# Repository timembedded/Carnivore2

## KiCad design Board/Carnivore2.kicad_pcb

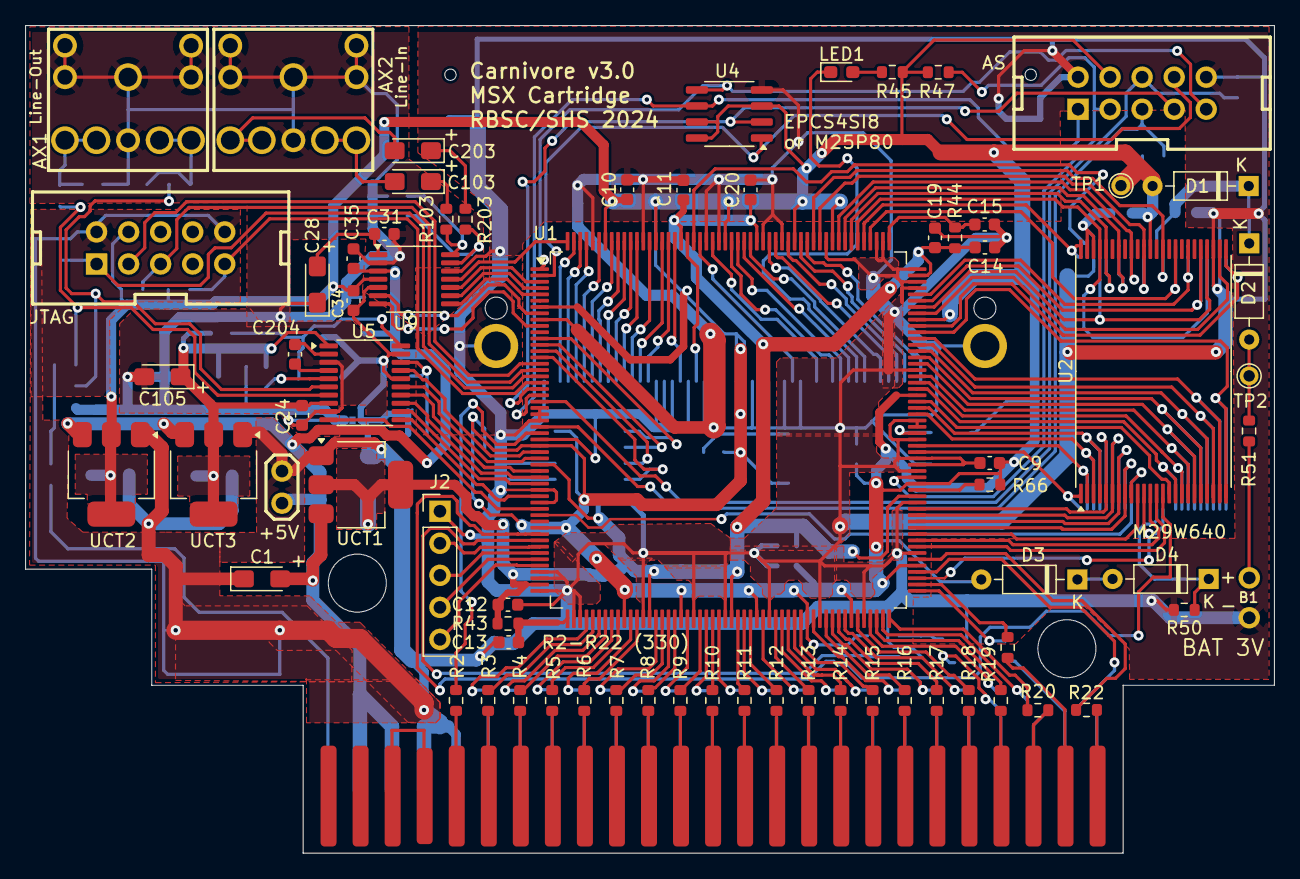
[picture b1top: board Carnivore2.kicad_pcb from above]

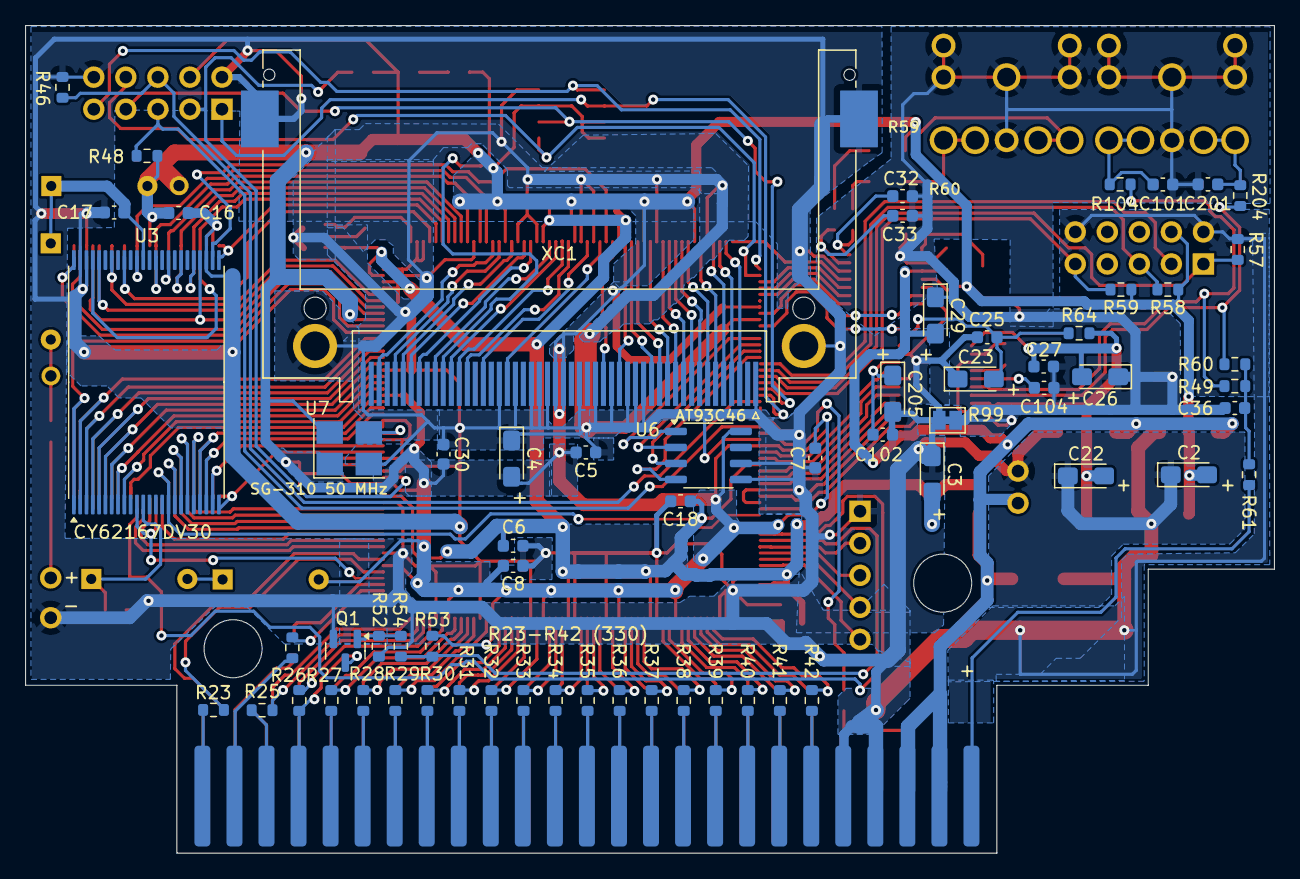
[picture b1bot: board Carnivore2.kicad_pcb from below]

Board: 2 copper layers, 99.0 x 65.6 mm, 139 parts (65 on the bottom side), 215 nets.

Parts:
AX1, AX2: SJ1-3523N; ST-222_1
B1: BAT 3V; BAT
C1, C2, C3, C4, C22, C23, C26, C28, C29, C105, C205: 10uF 10V; CP_EIA-3216-10_Kemet-I_Pad1.58x1.35mm_HandSolder
C5, C6, C7, C8, C9, C10, C11, C12, C13, C14, C15, C16, C17, C18, C19, C20, C24, C25, C27, C30, C31, C32, C33, C34, C35, C102: 100nF; C_0603_1608Metric
C36, C101, C201: 2.2nF; C_0603_1608Metric
C103, C203: 1uF 10V; CP_EIA-3216-10_Kemet-I_Pad1.58x1.35mm_HandSolder
C104, C204: 2.2uF; C_0603_1608Metric
D1, D2, D3, D4: 1N4148; D_DO-35_SOD27_P7.62mm_Horizontal
H1, H2: MountingHole
J1: Conn_01x02_Pin; JUMPER_1
J2: Conn_01x05_Pin; PinHeader_1x05_P2.54mm_Vertical
LED1: 150060YS75000; LED_0603_1608Metric_Pad1.05x0.95mm_HandSolder
Q1: MMBT3904-TP; SOT-23
R2, R3, R4, R5, R6, R7, R8, R9, R10, R11, R12, R13, R14, R15, R16, R17, R18, R19, R20, R21, R22, R23, R24, R25, R26, R27, R28, R29, R30, R31, R32, R33, R34, R35, R36, R37, R38, R39, R40, R41, R42: 330E; R_0603_1608Metric
R43, R44, R64: 10E; R_0603_1608Metric
R45: 220E; R_0603_1608Metric
R46, R47, R48, R50, R52, R66: 10k; R_0603_1608Metric
R49, R54, R60, R61, R104, R204: 470E; R_0603_1608Metric
R51, R57, R58, R59: 1k; R_0603_1608Metric
R53: 4k7; R_0603_1608Metric
R99: 0E; SolderJumper-2_P1.3mm_Bridged_Pad1.0x1.5mm
R103, R203: 75E; R_0603_1608Metric
TP1, TP2: TestPoint; TestPoint_THTPad_D1.5mm_Drill0.9mm
U1: EP2C8Q208C8N; PQFP-208_28x28mm_P0.5mm
U2: MX29LV640ETTI-70G; TSOP-I-48_18.4x12mm_P0.5mm
U3: RMLV1616AGSA-5S#KA0; TSOP-I-48_18.4x12mm_P0.5mm
U4: M25P80-VMN3TPB; SO-8_3.9x4.9mm_P1.27mm
U5: PCM5101APWR; TSSOP-20_4.4x6.5mm_P0.65mm
U6: AT93C46DN-SH-T; SO-8_3.9x4.9mm_P1.27mm
U7: SG3225CAN 50.0000M-TJGA6; SG3225CAN
U9: PCM1808PWR; TSSOP-14_4.4x5mm_P0.65mm
UCT1: AP2114HA-1.2TRG1; SOT-223
UCT2, UCT3: AP2111H-3.3TRG1; SOT-223
X1: EDGE50/MSX; EDGE50_MSX_1
X2, X3: 302-S101
XC1: 101D-TAAB-R01; CF-Card_101D-TAAB-R01

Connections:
/+1V2: C3.2 (PLUS), C6.2, C11.1, C12.2, C14.1, C18.1, C19.2, C20.1, R43.2, R44.1, U1.32 (VCCINT), U1.51 (VCCD_PLL1), U1.66 (VCCINT), U1.79 (VCCINT), U1.120 (VCCINT), U1.155 (VCCD_PLL2), U1.178 (VCCINT), U1.190 (VCCINT), UCT1.2 (OUT), UCT1.4 (OUT)
/+3.3V: C2.2 (PLUS), C4.2 (PLUS), C5.2, C7.2, C8.2, C9.2, C10.1, C16.2, C30.2, C34.2, D1.2 (A), D3.2 (A), R45.1, R47.2, R48.1, R53.1, R58.1, R59.1, R66.1, TP1.1, U1.7 (VCCIO1), U1.29 (VCCIO1), U1.42 (VCCIO1), U1.62 (VCCIO4), U1.71 (VCCIO4), U1.83 (VCCIO4), U1.91 (VCCIO4), U1.98 (VCCIO4), U1.109 (VCCIO3), U1.122 (VCCIO3), U1.136 (VCCIO3), U1.148 (VCCIO3), U1.166 (VCCIO2), U1.172 (VCCIO2), U1.183 (VCCIO2), U1.194 (VCCIO2), U1.202 (VCCIO2), U2.37 (VCC), U4.3 (~W), U4.7 (~HOLD), U4.8 (V_{CC}), U6.8 (VCC), U7.4 (VCC), U9.4 (VDD), UCT2.2 (OUT), UCT2.4 (OUT), X2.4, X3.4, XC1.13, XC1.38
/+3.3VDAC: C22.2 (PLUS), C24.2, C26.2 (PLUS), C27.2, C105.1 (PLUS), R64.2, U5.1 (CPVDD), U5.8 (AVDD), UCT3.2 (OUT), UCT3.4 (OUT)
/+5V: C1.2 (PLUS), C29.2 (PLUS), C35.2, J1.2, U9.3 (VCC), UCT1.3 (IN), UCT2.3 (IN), UCT3.3 (IN), X1.45, X1.47
/ADC_BCK: U1.5 (IO,_LVDS8p), U9.8 (BCK)
/ADC_DOUT: U1.4 (IO,_LVDS9n_(CLKUSR)), U9.9 (DOUT)
/ADC_LRCK: U1.10 (IO,_LVDS7n,_DQ1L1/_), U9.7 (LRCK)
/ADC_MD0: U1.3 (IO,_LVDS9p_(CRC_ERROR)), U9.10 (MD0)
/ADC_MD1: U1.208 (IO,_LVDS16n), U9.11 (MD1)
/ADC_SCKI: U1.8 (IO,_LVDS7p,_DQ1L0/_), U9.6 (SCKI)
/AGND: AX1.1, AX1.M (Mount), AX2.1, AX2.M (Mount), C24.1, C26.1 (MINUS), C27.1, C28.1 (MINUS), C29.1 (MINUS), C31.1, C32.1, C33.1, C35.1, C36.2, C101.1, C104.2, C105.2 (MINUS), C201.2, R99.2, U5.3 (CPGND), U5.9 (AGND), U9.2 (AGND)
/ASDO: U1.1 (IO,_(ASDO)), U4.5 (DQ0), X2.9
/CLC50: U1.130 (CLK6,_LVDSCLK3p_INPUT), U7.3 (OUT)
/DAC_BCK: U1.34 (IO,_DQ1L5/_), U5.13 (BCK)
/DAC_DEMP: U1.39 (IO,_LVDS3n,_DQ1L7/_), U5.10 (DEMP)
/DAC_DIN: U1.33 (IO,_LVDS6n,_DQ1L4/_), U5.14 (DIN)
/DAC_FLT: U1.37 (IO,_VREFB1N1), U5.11 (FLT)
/DAC_LRCK: U1.31 (IO,_LVDS7n), U5.15 (LRCK)
/DAC_SCK: U1.35 (IO,_LVDS2p,_DQ1L6/_), U5.12 (SCK)
/DAC_XSMT: U1.30 (IO,_LVDS7p,_(DPCLK1/DQS1L)/(DPCLK1/DQS1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), U5.17 (XSMT)
/DATA0: U1.20 (DATA0), U4.2 (DQ1), X2.7
/DCLK: U1.21 (DCLK), U4.6 (C), X2.1
/EECK: U1.13 (IO,_VREFB1N0), U6.2 (SK)
/EECS: U1.12 (IO,_LVDS6n,_DQ1L3/_), U6.1 (CS)
/EEDI: U1.14 (IO,_LVDS8p,_(DPCLK0/DQS0L)/(DPCLK0/DQS0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), U6.3 (DI)
/EEDO: U1.15 (IO,_LVDS8n), U6.4 (DO)
/GND: B1.NEG, C1.1 (MINUS), C2.1 (MINUS), C3.1 (MINUS), C4.1 (MINUS), C5.1, C6.1, C7.1, C8.1, C9.1, C10.2, C11.2, C12.1, C13.1, C14.2, C15.2, C16.1, C17.2, C18.2, C19.1, C20.2, C22.1 (MINUS), C23.1 (MINUS), C25.1, C30.1, C34.1, C102.1, C205.2 (MINUS), J1.1, J2.1, Q1.2 (E), R46.1, R50.2, R52.2, R57.1, R99.1, U1.9 (GND), U1.23 (CLK0,_LVDSCLK0p_INPUT), U1.24 (CLK1,_LVDSCLK0n_INPUT), U1.25 (GND), U1.28 (CLK3,_LVDSCLK1n_INPUT), U1.36 (GND), U1.38 (GND), U1.49 (GND), U1.50 (GND_PLL1), U1.52 (GND_PLL1), U1.54 (GNDA_PLL1), U1.55 (GND), U1.65 (GND), U1.73 (GND), U1.78 (GND), U1.85 (GND), U1.93 (GND), U1.100 (GND), U1.111 (GND), U1.119 (GND), U1.124 (GND), U1.125 (MSEL1), U1.126 (MSEL0), U1.129 (CLK7,_LVDSCLK3n_INPUT), U1.131 (CLK5,_LVDSCLK2n_INPUT), U1.132 (CLK4,_LVDSCLK2p_INPUT), U1.140 (GND), U1.153 (GND), U1.154 (GND_PLL2), U1.156 (GND_PLL2), U1.158 (GNDA_PLL2), U1.159 (GND), U1.167 (GND), U1.174 (GND), U1.177 (GND), U1.184 (GND), U1.186 (GND), U1.196 (GND), U1.204 (GND), U2.27 (GND), U2.46 (GND), U2.47 (~BYTE), U3.27 (GND), U3.46 (GND), U3.47 (~BYTE), U4.4 (V_{SS}), U5.16 (FMT), U5.19 (DGND), U6.5 (GND), U6.6 (ORG), U7.2 (GND), U9.5 (DGND), U9.12 (FMT), UCT1.1 (GND), UCT2.1 (GND), UCT3.1 (GND), X1.41, X1.43, X2.2, X2.10, X3.2, X3.10, XC1.1, XC1.8, XC1.9, XC1.10, XC1.11, XC1.12, XC1.14, XC1.15, XC1.16, XC1.17, XC1.33, XC1.39, XC1.50, XC1.51 (MH1), XC1.52 (MH2), XC1.53 (MH3), XC1.54 (MH4)
/HA0: U1.180 (IO,_LVDS29p), XC1.20
/HA1: U1.182 (IO,_LVDS28p), XC1.19
/HA2: U1.185 (IO,_LVDS26p,_DQ1T0/DQ1T9), XC1.18
/HD00: U1.179 (IO,_LVDS29n,_DM0T/(DM1T0/BWS#1T0)), XC1.21
/HD01: U1.176 (IO,_LVDS31p,__/DQ1T8), XC1.22
/HD02: U1.173 (IO,_LVDS33p,_DQ0T6/DQ1T6), XC1.23
/HD03: U1.207 (IO,_LVDS16p,_(DM1T/BWS#1T)/(DM1T1/BWS#1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), XC1.2
/HD04: U1.205 (IO,_LVDS17p,_DQ1T8/DQ1T17), XC1.3
/HD05: U1.201 (IO,_LVDS18n,_DQ1T6/DQ1T15), XC1.4
/HD06: U1.199 (IO,_LVDS19n), XC1.5
/HD07: U1.197 (IO,_LVDS21n), XC1.6
/HD08: U1.175 (IO,_LVDS31n,_DQ0T7/DQ1T7), XC1.47
/HD09: U1.171 (IO,_LVDS33n,_DQ0T5/DQ1T5), XC1.48
/HD10: U1.170 (IO,_VREFB2N0), XC1.49
/HD11: U1.206 (IO,_LVDS17n_(DEV_CLRn)), XC1.27
/HD12: U1.203 (IO,_LVDS18p,_DQ1T7/DQ1T16), XC1.28
/HD13: U1.200 (IO,_LVDS19p,_(DPCLK10/DQS1T)/(DPCLK10/D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), XC1.29
/HD14: U1.198 (IO,_LVDS21p), XC1.30
/HD15: U1.195 (IO,_LVDS23p,_DQ1T5/DQ1T14), XC1.31
/NCE: R46.2, U1.22 (nCE), X2.6
/NCONFIG: R48.2, U1.26 (nCONFIG), X2.5
/NCSO: U1.2 (IO,_(nCSO)), U4.1 (~S), X2.8
/RA00: U1.147 (IO,_LVDS39p,_DQ0R0/DQ1R0), U2.25 (A0), U3.48 (A16)
/RA01: U1.146 (IO,_LVDS39n,_DQ0R1/DQ1R1), U2.24 (A1), U3.1 (A15)
/RA02: U1.145 (IO,_VREFB3N0), U2.23 (A2), U3.2 (A14)
/RA03: U1.144 (IO,_LVDS42p,_DQ0R2/DQ1R2), U2.22 (A3), U3.3 (A13)
/RA04: U1.143 (IO,_LVDS42n,_DQ0R3/DQ1R3), U2.21 (A4), U3.4 (A12)
/RA05: U1.142 (IO,_LVDS44p,_DQ0R4/DQ1R4), U2.20 (A5), U3.5 (A11)
/RA06: U1.141 (IO,_LVDS44n,_DQ0R5/DQ1R5), U2.19 (A6), U3.6 (A10)
/RA07: U1.139 (IO,_LVDS45p,_DQ0R6/DQ1R6), U2.18 (A7), U3.7 (A9)
/RA08: U1.115 (IO,_LVDS51n,_DQ1R4/DQ1R13), U2.8 (A8), U3.17 (A17)
/RA09: U1.116 (IO,_LVDS51p,_DQ1R3/DQ1R12), U2.7 (A9), U3.18 (A7)
/RA10: U1.117 (IO,_VREFB3N1), U2.6 (A10), U3.19 (A6)
/RA11: U1.118 (IO,_DQ1R2/DQ1R11), U2.5 (A11), U3.20 (A5)
/RA12: U1.134 (IO,_LVDS47p,_(DPCLK7/DQS0R)/(DPCLK7/DQS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), U2.4 (A12), U3.21 (A4)
/RA13: U1.133 (IO,_LVDS47n,_DQ1R0/DQ1R9), U2.3 (A13), U3.22 (A3)
/RA14: U1.128 (IO,_LVDS48p,_(DPCLK6/DQS1R)/(DPCLK6/DQS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), U2.2 (A14), U3.23 (A2)
/RA15: U1.127 (IO,_LVDS48n,_DQ1R1/DQ1R10), U2.1 (A15), U3.24 (A1)
/RA16: U1.161 (IO,_LVDS37p,_DQ0T0/DQ1T0), U2.48 (A16), U3.25 (A0)
/RA17: U1.138 (IO,_LVDS45n,_DQ0R7/DQ1R7), U2.17 (A17), U3.8 (A8)
/RA18: U1.137 (IO,_LVDS46p,__/DQ1R8), U2.16 (A18), U3.9 (A19)
/RA19: U1.40 (IO,_LVDS2p,_DQ1L8/_), U2.9 (A19), U3.16 (A18)
/RA20: U1.114 (IO,_LVDS52p,_DQ1R5/DQ1R14), U2.10 (A20)
/RA21: U1.112 (IO,_LVDS53p,_DQ1R7/DQ1R16), U2.13 (A21)
/RDQ0: U1.151 (IO,_PLL2_OUTp), U2.29 (D0), U3.44 (D7)
/RDQ1: U1.152 (IO,_PLL2_OUTn), U2.31 (D1), U3.42 (D6)
/RDQ2: U1.160 (IO,_LVDS37n), U2.33 (D2), U3.40 (D5)
/RDQ3: U1.169 (IO,_LVDS34p,_(DPCLK8/DQS0T)/(DPCLK8/DQS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), U2.35 (D3), U3.38 (D4)
/RDQ4: U1.168 (IO,_LVDS34n), U2.38 (D4), U3.35 (D3)
/RDQ5: U1.165 (IO,_LVDS35p,_DQ0T4/DQ1T4), U2.40 (D5), U3.33 (D2)
/RDQ6: U1.164 (IO,_LVDS35n,_DQ0T3/DQ1T3), U2.42 (D6), U3.31 (D1)
/RDQ7: U1.163 (IO,_LVDS36p,_DQ0T2/DQ1T2), U2.44 (D7), U3.29 (D0)
/RDQ15A-1: U1.162 (IO,_LVDS36n,_DQ0T1/DQ1T1), U2.45 (D15), U3.45 (D15)
/RSW1: R15.2, U1.90 (IO,_LVDS61p,_DQ0B5/DQ1B5)
/RSW2: R25.1, U1.103 (IO,_LVDS57p)
/RVPPE: U1.43 (IO), U2.14 (Vpp/~WP)
/R~E: U1.149 (IO,_LVDS38n), U2.26 (~CE)
/R~G: U1.150 (IO,_LVDS38p), U2.28 (~OE), U3.28 (~OE)
/SLTSOUND: R61.2, X1.49
/SLT_A00: R9.2, U1.74 (IO,_LVDS68p,_DQ1B0/DQ1B9)
/SLT_A01: R36.1, U1.72 (IO,_LVDS68n,_DQ1B1/DQ1B10)
/SLT_A02: R8.2, U1.70 (IO,_LVDS68p,_DQ1B2/DQ1B11)
/SLT_A03: R37.1, U1.69 (IO,_LVDS70n,_DQ1B3/DQ1B12)
/SLT_A04: R7.2, U1.68 (IO,_LVDS70p,_DQ1B4/DQ1B13)
/SLT_A05: R38.1, U1.67 (IO,_VREFB4N1)
/SLT_A06: R12.2, U1.82 (IO,_LVDS64n)
/SLT_A07: R33.1, U1.81 (IO,_LVDS64p)
/SLT_A08: R11.2, U1.80 (IO)
/SLT_A09: R31.1, U1.87 (IO,_LVDS62p,_DQ0B7/DQ1B7)
/SLT_A10: R13.2, U1.86 (IO,_LVDS63n,__/DQ1B8)
/SLT_A11: R32.1, U1.84 (IO,_LVDS63p,_DM0B/(DM1B0/BWS#1B0))
/SLT_A12: R34.1, U1.77 (IO,_LVDS66n)
/SLT_A13: R10.2, U1.76 (IO,_LVDS66p)
/SLT_A14: R35.1, U1.75 (IO,_LVDS68n)
/SLT_A15: R14.2, U1.88 (IO,_LVDS62n,_DQ0B6/DQ1B6)
/SLT_CLC: R2.2, U1.27 (CLK2,_LVDSCLK1p_INPUT)
/SLT_D0: R6.2, U1.64 (IO,_LVDS74n)
/SLT_D1: R39.1, U1.63 (IO,_LVDS74p,_(DPCLK2/DQS1B)/(DPCLK2/DQS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)
/SLT_D2: R5.2, U1.61 (IO,_LVDS75n,_DQ1B5/DQ1B14)
/SLT_D3: R40.1, U1.60 (IO,_LVDS75p,_DQ1B6/DQ1B15)
/SLT_D4: R4.2, U1.59 (IO,_LVDS76n,_DQ1B7/DQ1B16)
/SLT_D5: R41.1, U1.58 (IO,_LVDS76p,_DQ1B8/DQ1B17)
/SLT_D6: R3.2, U1.57 (IO,_LVDS77p,_(DM1B/BWS#1B)/(DM1B1/BWS#1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)
/SLT_D7: R42.1, U1.56 (IO,_LVDS77n_(DEV_OE))
/TCK: R57.2, U1.18 (TCK), X3.1
/TDI: R59.2, U1.19 (TDI), X3.9
/TDO: U1.16 (TDO), X3.3
/TMS: R58.2, U1.17 (TMS), X3.5
/~CSRAM: U1.188 (IO,_LVDS25p,_DQ1T1/DQ1T10), U3.26 (~CE1)
/~HCS1: U1.193 (IO,_LVDS23n,_DQ1T4/DQ1T13), XC1.7
/~HCS3: U1.192 (IO,_VREFB2N1), XC1.32
/~HRD: U1.191 (IO,_LVDS24p,_DQ1T3/DQ1T12), XC1.34
/~HREG: U1.181 (IO,_LVDS28n), XC1.44
/~HRST: U1.187 (IO,_LVDS25n), XC1.41
/~HWR: U1.189 (IO,_LVDS24n,_DQ1T2/DQ1T11), XC1.35
/~RRB: U1.135 (IO,_LVDS46n,_DM0R/(DM1R0/BWS#1R0)), U2.15 (R~B)
/~RRP: U1.113 (IO,_LVDS52n,_DQ1R6/DQ1R15), U2.12 (~RP)
/~RWR: U1.107 (IO,_LVDS54n_(INIT_DONE)), U2.11 (~WE), U3.11 (~WE)
/~SLT_BUSDIR: R18.2, U1.99 (IO,_LVDS59n,_DQ0B1/DQ1B1)
/~SLT_CS1: R23.1, U1.108 (IO,_LVDS54p_(nCEO))
/~SLT_CS2: R22.2, U1.110 (IO,_LVDS53n,_DQ1R8/DQ1R17)
/~SLT_CS12: R24.1, U1.105 (IO,_LVDS56n)
/~SLT_INT: R19.2, U1.102 (IO,_LVDS58n)
/~SLT_IORQ: R28.1, U1.95 (IO,_LVDS60n)
/~SLT_M1: R27.1, U1.97 (IO,_LVDS59p,_DQ0B2/DQ1B2)
/~SLT_MREQ: R17.2, U1.96 (IO,_DQ0B3/DQ1B3)
/~SLT_RD: R16.2, U1.94 (IO,_LVDS60p,_(DPCLK4/DQS0B)/(DPCLK4/DQS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)
/~SLT_READY: R53.2, R54.1, U1.44 (IO,_LVDS0p)
/~SLT_RESET: R30.1, U1.89 (IO,_VREFB4N0)
/~SLT_RFSH: R20.2, U1.104 (IO,_LVDS57n)
/~SLT_SLTSEL: R21.2, U1.106 (IO,_LVDS56p,_(DM1R/BWS#1R)/(DM1R1/BWS#1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)
/~SLT_WAIT: R26.1, U1.101 (IO,_LVDS58p,_DQ0B0/DQ1B0)
/~SLT_WR: R29.1, U1.92 (IO,_LVDS61n,_DQ0B4/DQ1B4)
/~X_SLT_WAIT: Q1.3 (C), R26.2, X1.7
unnamed: AX1.2, AX1.3, C201.1, R204.2
unnamed: AX1.4, AX1.5, C101.2, R104.2
unnamed: B1.POS, R51.2
unnamed: C23.2 (PLUS), C25.2, R64.1, U5.20 (DVDD)
unnamed: C28.2 (PLUS), C31.2, U9.1 (VREF)
unnamed: C36.1, R49.2, R60.2, R61.1
unnamed: AX2.4, AX2.5, C103.2 (MINUS)
unnamed: C103.1 (PLUS), R103.2
unnamed: AX2.2, AX2.3, C203.2 (MINUS)
unnamed: C203.1 (PLUS), R203.2
unnamed: C102.2, C205.1 (PLUS), U5.18 (LDOO)
unnamed: C17.1, D1.1 (K), D2.1 (K), U3.37 (VCC)
unnamed: D2.2 (A), R51.1, TP2.1
unnamed: D3.1 (K), D4.2 (A)
unnamed: D4.1 (K), R50.1, U3.12 (CE2)
unnamed: J2.2, U1.45 (IO,_LVDS0n)
unnamed: J2.3, U1.46 (IO)
unnamed: J2.4, U1.47 (IO,_PLL1_OUTp)
unnamed: J2.5, U1.48 (IO,_PLL1_OUTn)
unnamed: LED1.2 (A), R45.2
unnamed: LED1.1 (K), XC1.45
unnamed: Q1.1 (B), R52.1, R54.2
unnamed: R2.1, X1.42
unnamed: R3.1, X1.40
unnamed: R4.1, X1.38
unnamed: R5.1, X1.36
unnamed: R6.1, X1.34
unnamed: R7.1, X1.32
unnamed: R8.1, X1.30
unnamed: R9.1, X1.28
unnamed: R10.1, X1.26
unnamed: R11.1, X1.24
unnamed: R12.1, X1.22
unnamed: R13.1, X1.20
unnamed: R14.1, X1.18
unnamed: R15.1, X1.16
unnamed: R16.1, X1.14
unnamed: R17.1, X1.12
unnamed: R18.1, X1.10
unnamed: R19.1, X1.8
unnamed: R20.1, X1.6
unnamed: R21.1, X1.4
unnamed: R22.1, X1.2
unnamed: R23.2, X1.1
unnamed: R24.2, X1.3
unnamed: R25.2, X1.5
unnamed: R27.2, X1.9
unnamed: R28.2, X1.11
unnamed: R29.2, X1.13
unnamed: R30.2, X1.15
unnamed: R31.2, X1.17
unnamed: R32.2, X1.19
unnamed: R33.2, X1.21
unnamed: R34.2, X1.23
unnamed: R35.2, X1.25
unnamed: R36.2, X1.27
unnamed: R37.2, X1.29
unnamed: R38.2, X1.31
unnamed: R39.2, X1.33
unnamed: R40.2, X1.35
unnamed: R41.2, X1.37
unnamed: R42.2, X1.39
unnamed: R47.1, U1.123 (CONF_DONE), X2.3
unnamed: R66.2, U1.121 (nSTATUS)
unnamed: C13.2, R43.1, U1.53 (VCCA_PLL1)
unnamed: C15.1, R44.2, U1.157 (VCCA_PLL2)
unnamed: C204.2, U5.4 (CAPM)
unnamed: C204.1, U5.2 (CAPP)
unnamed: R49.1, R104.1, U5.6 (OUTL)
unnamed: R60.1, R204.1, U5.7 (OUTR)
unnamed: C104.1, U5.5 (VNEG)
unnamed: C33.2, R203.1, U9.13 (VinL)
unnamed: C32.2, R103.1, U9.14 (VinR)
unnamed: X1.44, X1.46

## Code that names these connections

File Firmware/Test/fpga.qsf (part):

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set_global_assignment -name DEVICE_FILTER_PACKAGE "ANY QFP"

set_location_assignment PIN_3 -to ADC_MD[0]
set_location_assignment PIN_4 -to ADC_DOUT
set_location_assignment PIN_5 -to ADC_BCK
set_location_assignment PIN_8 -to ADC_SCKI
set_location_assignment PIN_10 -to ADC_LRCK
set_location_assignment PIN_12 -to EECS
set_location_assignment PIN_13 -to EECK
set_location_assignment PIN_14 -to EEDI
set_location_assignment PIN_15 -to EEDO
set_location_assignment PIN_27 -to pSltClk
set_location_assignment PIN_30 -to DAC_XSMT
set_location_assignment PIN_31 -to DAC_LRCK
set_location_assignment PIN_33 -to DAC_DIN
set_location_assignment PIN_34 -to DAC_BCK
set_location_assignment PIN_35 -to DAC_SCK
set_location_assignment PIN_37 -to DAC_FLT
set_location_assignment PIN_39 -to DAC_DEMP
set_location_assignment PIN_40 -to pFlAdr[20]
set_location_assignment PIN_43 -to pFlVpp
set_location_assignment PIN_44 -to J2_2
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
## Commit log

2024-02-20 Converted schematic and pcb to KiCad
2024-02-23 Schematic and pcb conversion cleanup and rework
2024-02-25 Fixed lots of design rule check errors and warnings in pcb Including some serious errors: Lots of fpga GND pins unconnected, C28 connected to wrong net
2024-02-26 Created local footprint library
2024-02-26 Changed fpga from EP2C5 to EP2C8
2024-03-11 Changed audio DAC to modern type, added audio input, updated footprints
2024-03-19 Updated more footprints 3D view complete
2024-03-25 Some last details
2024-03-29 Last update before ordering PCB
2024-04-03 Corrections in silkscreen for wrong direction of some capacitors and all diodes
2024-04-26 Firmware changes for new DAC And updated to Quartus 13.0
2024-04-26 Made BootMenu build in sjasm
2024-04-26 Adapted utils for different flash used And made them build with sjasm
2024-04-26 Test firmware currently only for testing the audio dac
2024-10-19 Added work-in progress redesigned firmware
2024-10-22 Implemented Sunrise IDE (CompactFlash)
2024-10-24 Implemented memory mapper
2024-10-25 Improved timing by adding one clock latency
2024-10-28 Added proof-of-concept keyboard controlled configuration manager
2024-10-31 Work in progress SCC implementation
2024-11-13 Implemented carnivore mega mapper Most but not all registers implemented
2024-11-14 Set mapper defaults to defaults in boot menu and reversed F5 key meaning Now press F5 to enter menu, by default no menu
2024-11-17 Added copyright headers
2024-11-17 Updated documentation and modified c2ramldr to directly reboot into the game
2024-11-17 Improved c2ramldr
2024-11-17 Implemented new card detect register and used it in c2ramldr
2024-11-20 Simplified registers, implemented not-expanded setting and fixed bug in soft reset detect
2024-11-20 Improved c2ramldr and made start of separating common functions to include files
2024-12-24 Some cleanup of c2ramldr
2024-12-24 Implemented C version of the c2ramldr tool And added some useful options to it Not fully tested yet
2024-12-24 c2ramldr.c: cleanup and removed some apparently dead code
2024-12-25 Added build output of C-utils
2024-12-28 Added dos2 support to c2ramldr tool auto-detect and use dos2 if available, else uses dos1 functions
2024-12-29 Improved make stuff and moved unittests to separate directory
2024-12-29 Multi-core build problem fix
2025-02-27 Hardware modification to delay Z80 startup until FPGA is configured Needed on FS-A1W(S)X models
2025-10-16 Minor improvements
2025-11-08 Improved slot wait

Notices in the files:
Firmware/Test/fpga.qsf:
Copyright (C) 1991-2009 Altera Corporation
